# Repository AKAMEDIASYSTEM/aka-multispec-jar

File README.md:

EINK STARTER MONITOR
===

See full blogpost [here](https://hi-hi-hi.com/food/projects/2021/06/18/jar.html)

Tracks height of starter with a VL6180 i2c distance sensor, and CO2/temperature/humidity with an SCD30. A small MOSFET circuit drives a little fan to more consistently sample the CO2.

Built around the LILYGO EINK [module](https://www.aliexpress.com/item/32869729970.html)

BOM
-------

- LILYGO EINK [module](https://www.aliexpress.com/item/32869729970.html)
- Adafruit Qwiic [SCD30](https://www.adafruit.com/product/4867)
- Adafruit [VL6180](https://www.adafruit.com/product/3316)
- 2N7000 N-Channel [MOSFET](https://www.digikey.com/en/products/detail/fairchild-semiconductor/2N7000/13430333)
- 420mAh [LiPo](https://www.adafruit.com/product/4236)
- wee tiny Fan ([this](https://www.sparkfun.com/products/15504) or any equivalent, smaller the better)
- M2 screws, 12 to 20mm long, and nuts
- Peanut butter container and 2 lids

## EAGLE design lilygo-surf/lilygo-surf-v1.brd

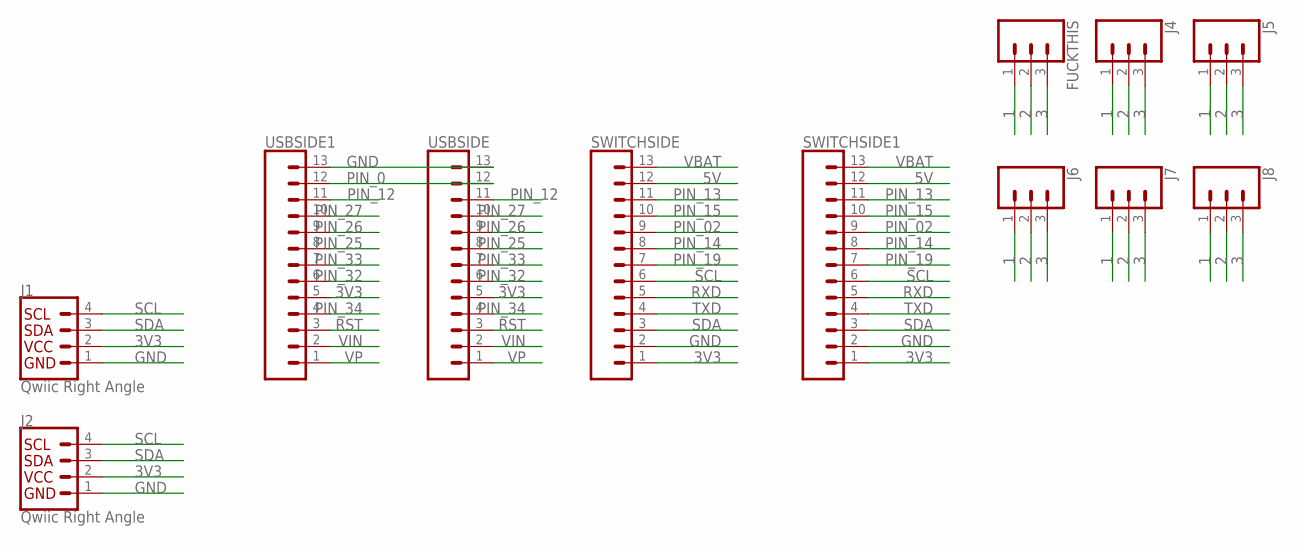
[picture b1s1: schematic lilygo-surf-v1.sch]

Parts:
FUCKTHIS: CONN_03; 1X03
J1, J2: Qwiic Right Angle; 1X04_1MM_RA
J4, J5, J6, J7, J8: CONN_03; 1X03
SWITCHSIDE, SWITCHSIDE1: CONN_13LOCK; 1X13_LOCK
USBSIDE, USBSIDE1: CONN_13LOCK; 1X13_LOCK

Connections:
1: FUCKTHIS.1, J4.1, J5.1, J6.1, J7.1, J8.1
2: FUCKTHIS.2, J4.2, J5.2, J6.2, J7.2, J8.2
3: FUCKTHIS.3, J4.3, J5.3, J6.3, J7.3, J8.3
3V3: J1.2, J2.2, SWITCHSIDE.1, SWITCHSIDE1.1, USBSIDE.5, USBSIDE1.5
5V: SWITCHSIDE.12, SWITCHSIDE1.12
GND: J1.1, J2.1, SWITCHSIDE.2, SWITCHSIDE1.2, USBSIDE.13, USBSIDE1.13
PIN_0: USBSIDE.12, USBSIDE1.12
PIN_02: SWITCHSIDE.9, SWITCHSIDE1.9
PIN_12: USBSIDE.11, USBSIDE1.11
PIN_13: SWITCHSIDE.11, SWITCHSIDE1.11
PIN_14: SWITCHSIDE.8, SWITCHSIDE1.8
PIN_15: SWITCHSIDE.10, SWITCHSIDE1.10
PIN_19: SWITCHSIDE.7, SWITCHSIDE1.7
PIN_25: USBSIDE.8, USBSIDE1.8
PIN_26: USBSIDE.9, USBSIDE1.9
PIN_27: USBSIDE.10, USBSIDE1.10
PIN_32: USBSIDE.6, USBSIDE1.6
PIN_33: USBSIDE.7, USBSIDE1.7
PIN_34: USBSIDE.4, USBSIDE1.4
RST: USBSIDE.3, USBSIDE1.3
RXD: SWITCHSIDE.5, SWITCHSIDE1.5
SCL: J1.4, J2.4, SWITCHSIDE.6, SWITCHSIDE1.6
SDA: J1.3, J2.3, SWITCHSIDE.3, SWITCHSIDE1.3
TXD: SWITCHSIDE.4, SWITCHSIDE1.4
VBAT: SWITCHSIDE.13, SWITCHSIDE1.13
VIN: USBSIDE.2, USBSIDE1.2
VP: USBSIDE.1, USBSIDE1.1

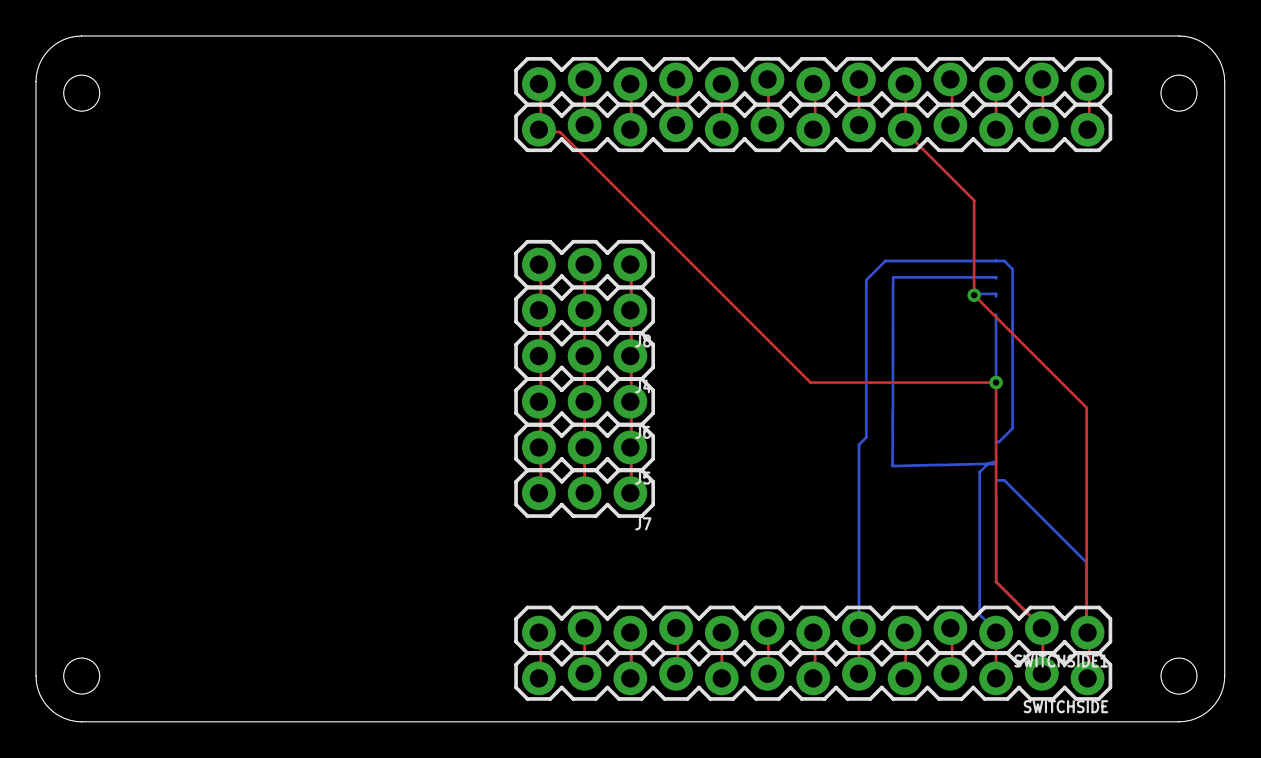
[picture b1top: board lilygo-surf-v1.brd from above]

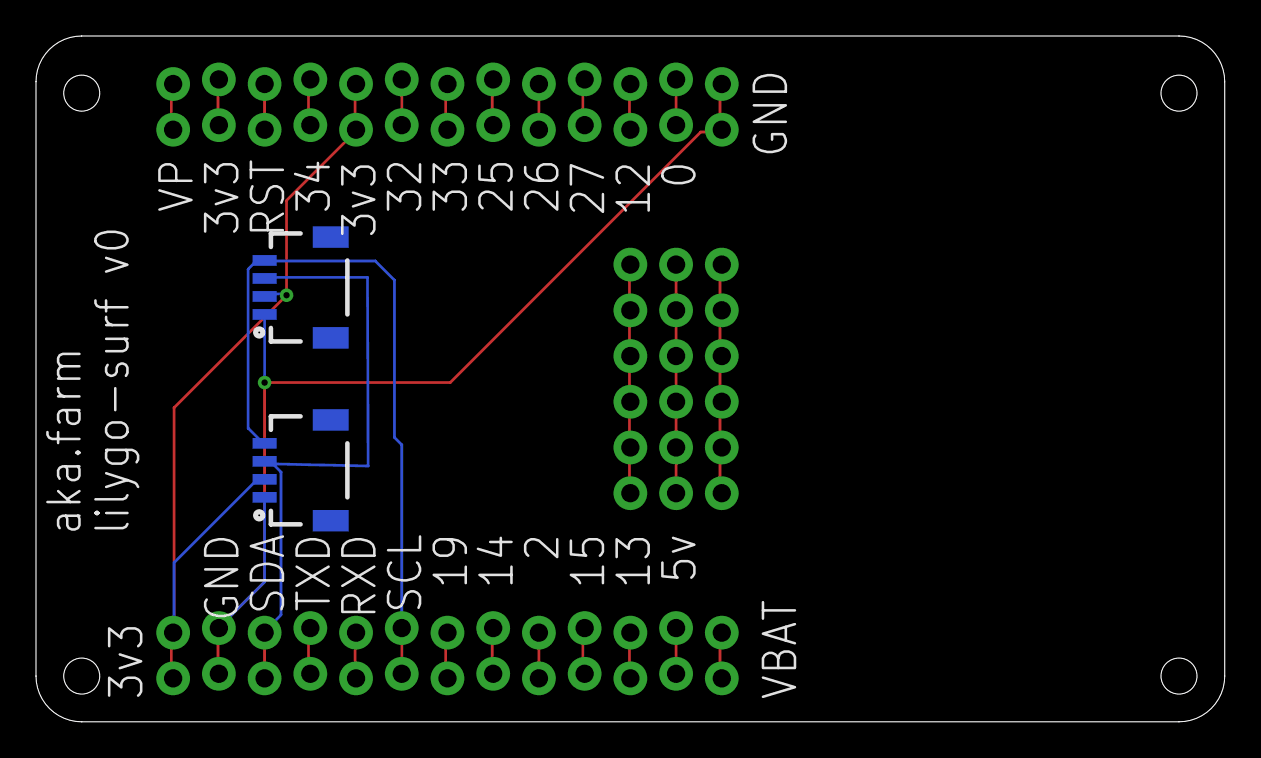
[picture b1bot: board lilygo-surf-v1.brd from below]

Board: 2 copper layers, 66.0 x 38.1 mm, 12 parts (2 on the bottom side), 27 nets.

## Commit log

2021-06-06 first commit to this repo. Soon I will remove lots of distance-sensor code.
2021-06-06 updated to track all 4 sensor channels and remove outdated libraries
2021-06-07 now sending mqtt to casepi.local mycodo instance
2021-06-11 removing SD card code, removing qwiic powerswitch hack code, making mqtt topics device-specific
2021-06-11 update specific eink screen library, new batch
2021-06-11 tested and implemented fan control via 2n7000 mosfet rather than absurd qwiic contrivance. changing MQTT topic names, still not connecting properly to mycodo
2021-06-13 got mqtt to mycodo working again, mycodo side needed to know clientID, which is by default String(ESP_getChipId(), HEX) in the asyncmqtt library for future reference
2021-06-18 adding small readme
2021-06-18 ugh typoes
2021-06-18 Create LICENSE
2021-06-18 adding PCB
2021-06-28 made drawGraph much more flexible
2021-07-02 trying to modify client id
2021-11-15 small update to ssid broadcast when starting up

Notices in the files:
parts and their libraries:
SparkFun-Connectors: Licensing: Creative Commons ShareAlike 4.0 International - https://creativecommons.org/licenses/by-sa/4.0
